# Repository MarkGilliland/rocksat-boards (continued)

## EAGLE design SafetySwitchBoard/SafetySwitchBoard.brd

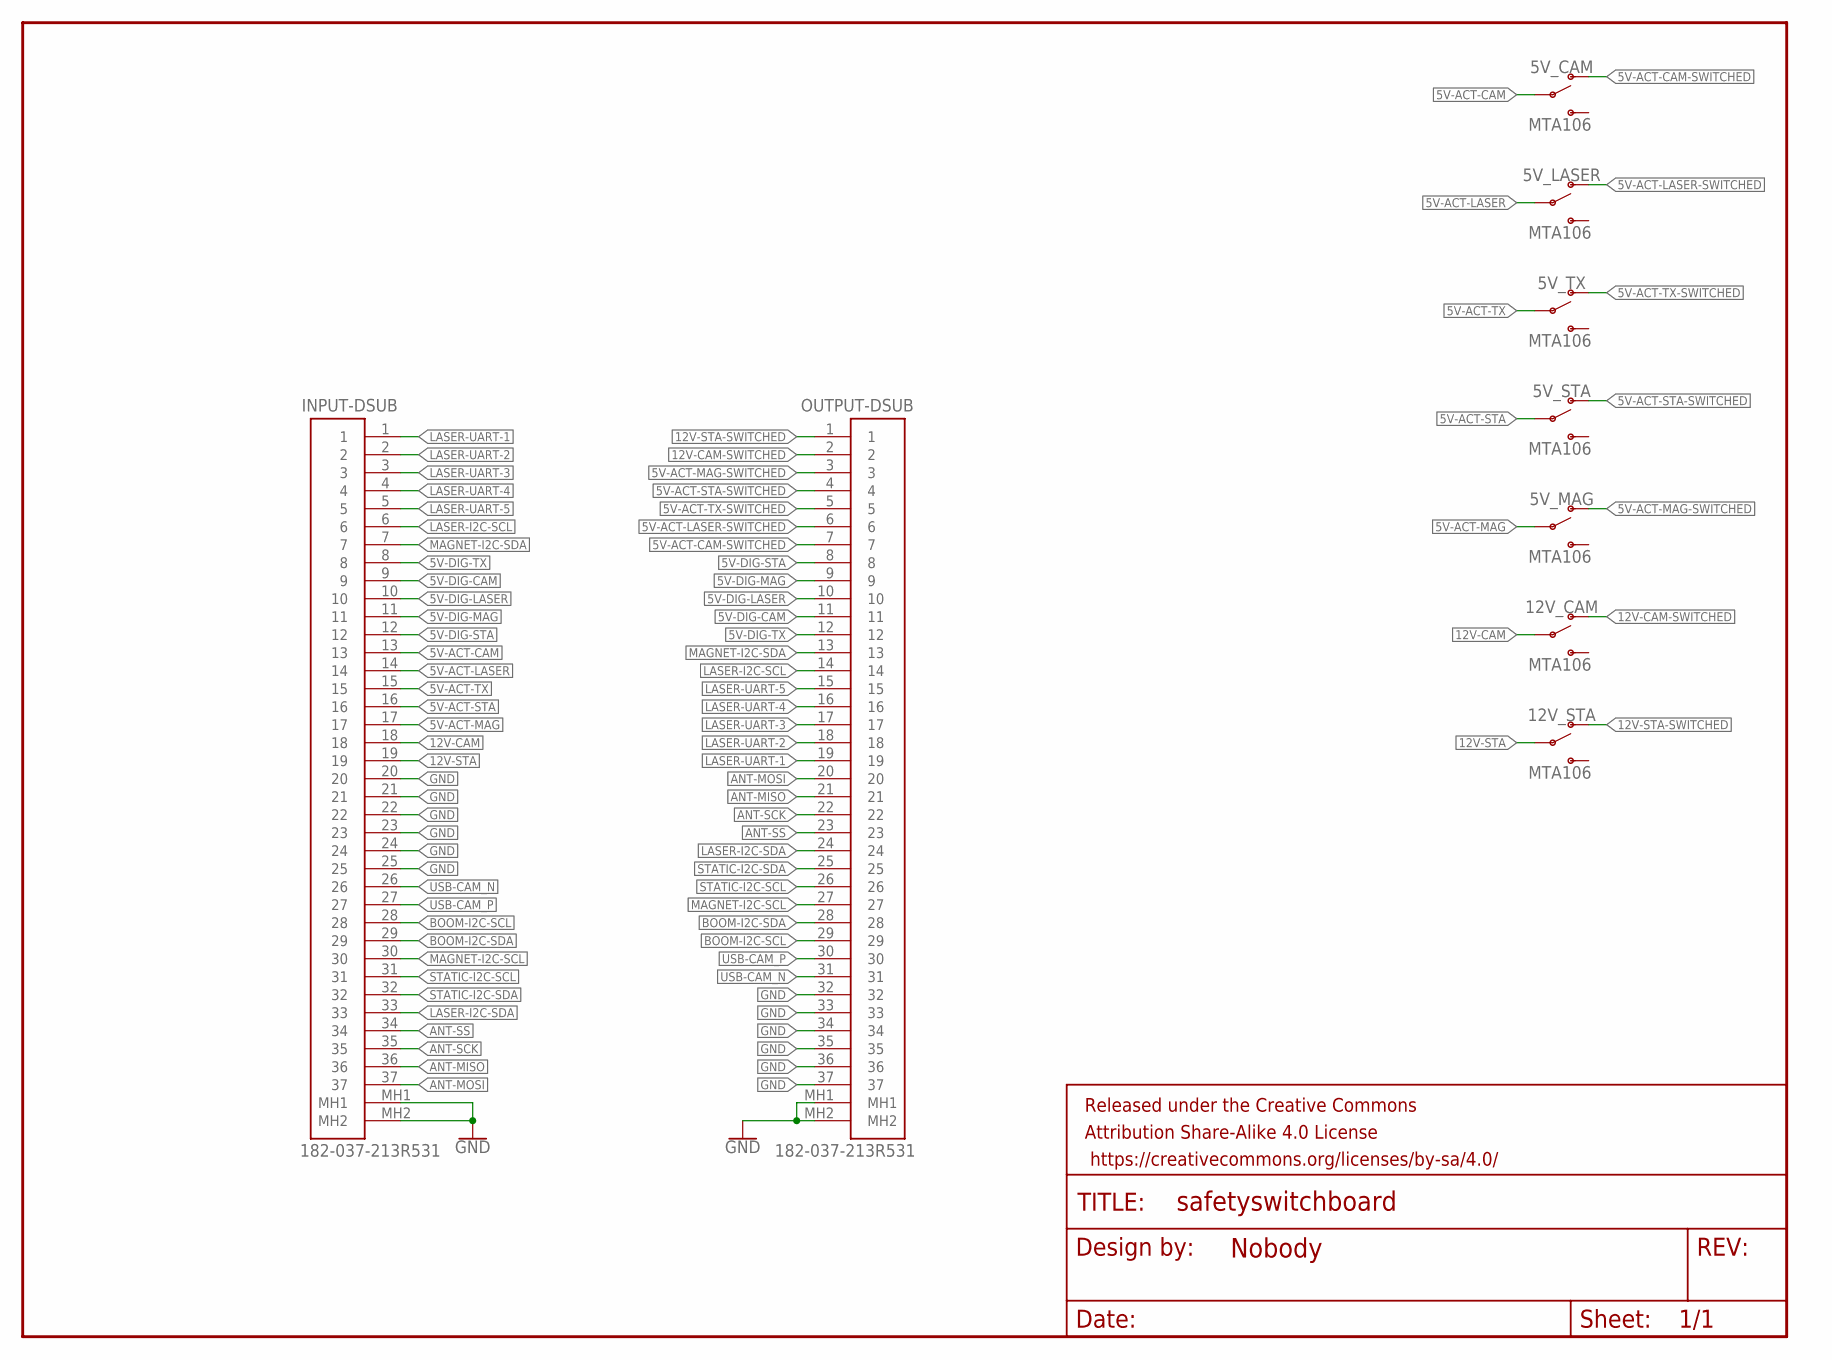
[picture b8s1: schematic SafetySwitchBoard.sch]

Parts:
5V_CAM, 5V_LASER, 5V_MAG, 5V_STA, 5V_TX, 12V_CAM, 12V_STA: MTA106
FRAME1: FRAME-LETTERNO_PACKAGE; DUMMY
INPUT-DSUB: 182-037-213R531
OUTPUT-DSUB: 182-037-213R531

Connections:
5V-ACT-CAM: 5V_CAM.P$1, INPUT-DSUB.13
5V-ACT-CAM-SWITCHED: 5V_CAM.P$2 (O), OUTPUT-DSUB.7
5V-ACT-LASER: 5V_LASER.P$1, INPUT-DSUB.14
5V-ACT-LASER-SWITCHED: 5V_LASER.P$2 (O), OUTPUT-DSUB.6
5V-ACT-MAG: 5V_MAG.P$1, INPUT-DSUB.17
5V-ACT-MAG-SWITCHED: 5V_MAG.P$2 (O), OUTPUT-DSUB.3
5V-ACT-STA: 5V_STA.P$1, INPUT-DSUB.16
5V-ACT-STA-SWITCHED: 5V_STA.P$2 (O), OUTPUT-DSUB.4
5V-ACT-TX: 5V_TX.P$1, INPUT-DSUB.15
5V-ACT-TX-SWITCHED: 5V_TX.P$2 (O), OUTPUT-DSUB.5
5V-DIG-CAM: INPUT-DSUB.9, OUTPUT-DSUB.11
5V-DIG-LASER: INPUT-DSUB.10, OUTPUT-DSUB.10
5V-DIG-MAG: INPUT-DSUB.11, OUTPUT-DSUB.9
5V-DIG-STA: INPUT-DSUB.12, OUTPUT-DSUB.8
5V-DIG-TX: INPUT-DSUB.8, OUTPUT-DSUB.12
12V-CAM: 12V_CAM.P$1, INPUT-DSUB.18
12V-CAM-SWITCHED: 12V_CAM.P$2 (O), OUTPUT-DSUB.2
12V-STA: 12V_STA.P$1, INPUT-DSUB.19
12V-STA-SWITCHED: 12V_STA.P$2 (O), OUTPUT-DSUB.1
ANT-MISO: INPUT-DSUB.36, OUTPUT-DSUB.21
ANT-MOSI: INPUT-DSUB.37, OUTPUT-DSUB.20
ANT-SCK: INPUT-DSUB.35, OUTPUT-DSUB.22
ANT-SS: INPUT-DSUB.34, OUTPUT-DSUB.23
BOOM-I2C-SCL: INPUT-DSUB.28, OUTPUT-DSUB.29
BOOM-I2C-SDA: INPUT-DSUB.29, OUTPUT-DSUB.28
GND: INPUT-DSUB.20, INPUT-DSUB.21, INPUT-DSUB.22, INPUT-DSUB.23, INPUT-DSUB.24, INPUT-DSUB.25, INPUT-DSUB.MH1, INPUT-DSUB.MH2, OUTPUT-DSUB.32, OUTPUT-DSUB.33, OUTPUT-DSUB.34, OUTPUT-DSUB.35, OUTPUT-DSUB.36, OUTPUT-DSUB.37, OUTPUT-DSUB.MH1, OUTPUT-DSUB.MH2
LASER-I2C-SCL: INPUT-DSUB.6, OUTPUT-DSUB.14
LASER-I2C-SDA: INPUT-DSUB.33, OUTPUT-DSUB.24
LASER-UART-1: INPUT-DSUB.1, OUTPUT-DSUB.19
LASER-UART-2: INPUT-DSUB.2, OUTPUT-DSUB.18
LASER-UART-3: INPUT-DSUB.3, OUTPUT-DSUB.17
LASER-UART-4: INPUT-DSUB.4, OUTPUT-DSUB.16
LASER-UART-5: INPUT-DSUB.5, OUTPUT-DSUB.15
MAGNET-I2C-SCL: INPUT-DSUB.30, OUTPUT-DSUB.27
MAGNET-I2C-SDA: INPUT-DSUB.7, OUTPUT-DSUB.13
STATIC-I2C-SCL: INPUT-DSUB.31, OUTPUT-DSUB.26
STATIC-I2C-SDA: INPUT-DSUB.32, OUTPUT-DSUB.25
USB-CAM_N: INPUT-DSUB.26, OUTPUT-DSUB.31
USB-CAM_P: INPUT-DSUB.27, OUTPUT-DSUB.30

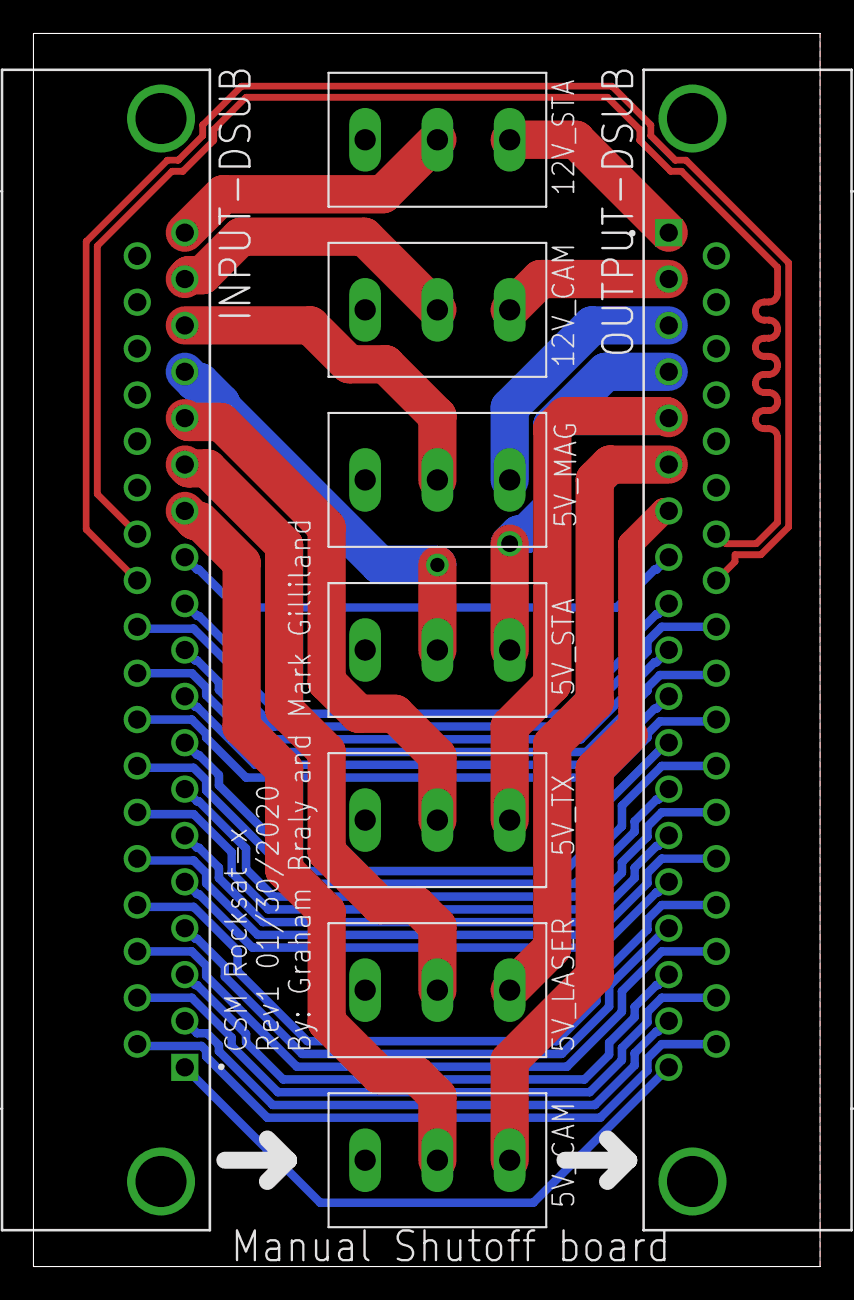
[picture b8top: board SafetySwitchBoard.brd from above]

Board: 2 copper layers, 47.0 x 73.7 mm, 10 parts (0 on the bottom side), 39 nets.

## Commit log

2019-10-22 Created blank project, added CUI part library
2019-10-22 Added sparkfun library. Added 3.3Vreg to PwrMngLib, added a fairly blank schematic to the power management proj
2019-10-22 Wired up CUI modules, added blank sheets for other devices
2019-10-23 Added board file
2019-10-23 Added resistor networks
2019-10-23 Added Teensy, Mux, OpAmp, Molex connectors
2019-10-23 Changed resistor look for resistor network. Split current amp into single symbols
2019-10-23 Added MOSFET to lib. Added Teensy to schem
2019-10-23 Created control for Laser and TX. Minor teaks to current amp part.
2019-10-23 Created very rough layout of large parts on board. Added mounting holes.
2019-10-23 Updated some schem sybmols, wired up the MOSFET for cam and static
2019-10-24 Added notes and minor changes
2019-10-24 Test: tried changing hole diameter on this branch while other branch is modified
2019-10-24 Test: Moved holes
2019-10-24 Added useless LED for test, names some nets.
2019-10-24 Test 2: Moved holes
2019-10-24 Finalized schematic. Ready for board layout
2019-10-24 Initial board layout
2019-11-05 Added beginnings of Subsystem control board. Still needs MOSFET and routing.
2019-11-07 Added Mosfet to library. First rev of subsystem control board finished and routed.
2019-11-07 Forgot to add updated part library.
2019-12-06 Redid MOSFET symbol. MOSFET is now Nchan on Low-side.
2019-12-06 Added AKA to nameplate
2019-12-08 Intial boom control board schematic and layout. Updated subystsem control board.
2019-12-08 minor aesthetic adjustments to boom control board schem
2019-12-08 added db 37 and db25
2019-12-10 Added RF module to Boom Control Board.
2019-12-17 Power Board: Removed molex connectors, started routing signals
2019-12-18 Added RPi-card part/package. USB ports need editing
2019-12-18 Added design rules for PCBWay and SilverCircuits
2019-12-18 changed USB footprint for manufacturability
2019-12-18 added initial boards and parts for both boards
2019-12-18 Added data control boards, further refined USB part
2019-12-18 Added USB lines for the camera
2019-12-18 Mechanical design of RPi Holder board nearly done. Power treaces routed
2019-12-19 Added micro-d25 connectors to lib, added to schem
2019-12-19 Added some parts and routes. Exposed bottom of teensy
2019-12-19 Schematic mostly done. Needs rpi backplane mating header, and a bunch of jumpers
2019-12-19 Added second MOSFET to subsystem control board and rerouted.
2019-12-20 Breakout headers added to Experiment Control board.
2019-12-20 Added USB to all RPi boards. Rearranged mechanical design slightly
2019-12-20 Ready for Diff Pair routing
2019-12-20 Added Pin labels to new breakout pins
2019-12-20 Added proj files, routed some traces on RPi backplane
2019-12-20 Added labels. Almost ready for manufacture
2019-12-20 Rearranged DataControl-Teensy
2019-12-20 Mirrored RPi components. Some traces routed
2019-12-20 Added jumper selection for sda/scl and wired rs232 converter
2019-12-21 Finished routing Boom Control Board, added breakout points and labels. Swapped L298 for SMD part and swapped to dual SMD/TH RF Module footprint.
2019-12-21 Improved Molex connector footprints.
2019-12-21 Data control schem ready for double-check
2019-12-22 Added ground merger fake part
2019-12-22 Minor schematic changes, added GND merges and header for LIDAR
2019-12-22 Lots of Labels added, GND connections added, component labels embiggened, traces rerouted.
2019-12-22 Significant routing progress
2019-12-22 Fully routed. Needs minor changes
2019-12-22 Added mounting holes and rounded corners
2019-12-22 Teensy board ready for double check
2019-12-22 Reorganized MOSFETs
2019-12-22 Did some stuff
2019-12-22 Moved some labels
2019-12-22 Changed silkscreen for clarity
2019-12-22 Started project for PowerTestbench
2019-12-22 Started power test bench schem, mostly done
2019-12-22 Board mostly routed. Added indicator LEDs and protection diodes
2019-12-22 routed protection diodes
2019-12-22 Ready to manufacture
2019-12-22 Minor changes, added attribution
2019-12-22 Added BOMs
2019-12-23 Added caps on power busses. Enlarged power traces
2019-12-23 Added jumper
2019-12-23 Added files neccessary to manufacture
2020-01-21 Replace resistor networks.
2020-01-21 Moved components around on board. Updated power input header
2020-01-23 Added CAM files
2020-01-23 Rearranged MOSFET groups to assist with routing
2020-01-23 Added sparkfun design rules
2020-01-23 Gateswapped the op-amps around so that we get easier routing
2020-01-23 CurrentAmps routed
2020-01-24 More routing
2020-01-24 Added comment
2020-01-26 Some traces routed on Pwr Distrib. board
2020-01-27 Amost all of pwr board routed. Pushing for safety before MOSFET control pin rework.
2020-01-27 Completed routing of power board. Ready for checking.
2020-01-28 Almost done, but does not have temp sensors
2020-01-28 Added temp sensors. Rerouted Digital lines to db25.
2020-01-28 very minor fix
2020-01-28 Added camera connector
2020-01-28 Worked on camera board
2020-01-28 Initial Rev2 for Boom and Exp. Control boards
2020-01-29 added mechanical drawing to layer 200
2020-01-30 added note about MSB/LSB
2020-01-30 Minor improvements to Bomom and Exp. boards. Created safety switch board and switch footprint for MTA106
2020-01-31 Refined SafetySwitchBoard
2020-02-04 Slight mods to switch board
2020-02-06 Switch board diff pair rerouted
2020-02-06 Added rev2 , including Teensy supply voltage and other minor issues.
2020-02-06 Finished RPi board rev 2.
2020-02-06 Moved some files around. Made progress on power management board
2020-02-06 Gerbers for RPi board made
2020-02-06 Added board-edge db15, ready to route camera signal converter board
2020-02-07 Routed camera converter board|
2020-02-07 Panellized camera boards into 4-packs, uploaded gerbers to JLC
2020-02-07 Implemented ANT-BUSY signal to replace 5V supply on lidar
2020-02-07 Routed data control board
2020-02-07 Made a nice silkscreen for power board
2020-02-07 edits to exp and boom control boards
2020-02-07 New 3x3 panelized camera converter boards
2020-02-07 Added gerbers
2020-02-25 Added mechanical outline of DBs
2020-03-01 Restored layers to nearly default
2020-05-25 Schematic and parts created
2020-05-25 Partially Routed
2020-10-24 Initial upload of MicroD-25 breakout board
2020-10-24 Complete routing of Micro-D25 breakout board. Coordinate with MechE and send to manufacture
